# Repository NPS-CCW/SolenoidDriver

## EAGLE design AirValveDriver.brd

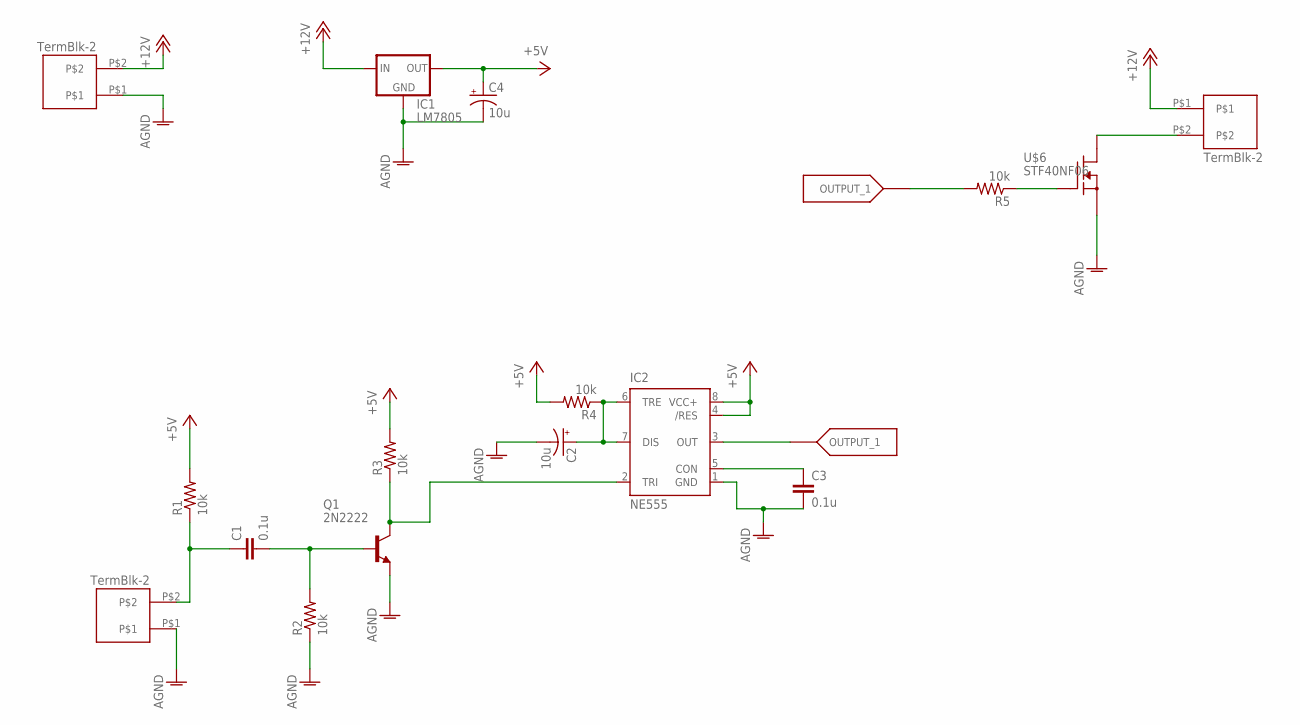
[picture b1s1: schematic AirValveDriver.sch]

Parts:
C1, C3: 0.1u; CCERAMIC_PKG
C2, C4: 10u; CPOL_PKG
IC1: LM7805; 78XXL
IC2: NE555; DIL-08
Q1: 2N2222; TO18
R1, R2, R3, R4, R5: 10k; RESISTOR_PKG
U$2, U$5: TB2; TB2_PKG
U$3: Pwr; TB2_PKG
U$6: STF40NF06; TO220H

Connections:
+5V: C4.+, IC1.OUT, IC2.4 (/RES), IC2.8 (VCC+), R1.2, R3.2, R4.2
+12V: IC1.IN, U$2.P$1, U$3.P$2
AGND: C2.-, C3.2, C4.-, IC1.GND, IC2.1 (GND), Q1.1 (E), R2.1, U$3.P$1, U$5.P$1, U$6.3 (S)
unnamed: C3.1, IC2.5 (CON)
unnamed: R5.1, U$6.1 (G)
unnamed: U$2.P$2, U$6.2 (D)
unnamed: C1.1, R1.1, U$5.P$2
unnamed: C1.2, Q1.2 (B), R2.2
unnamed: IC2.2 (TRI), Q1.3 (C), R3.1
unnamed: C2.+, IC2.6 (TRE), IC2.7 (DIS), R4.1
OUTPUT_1: IC2.3 (OUT), R5.2

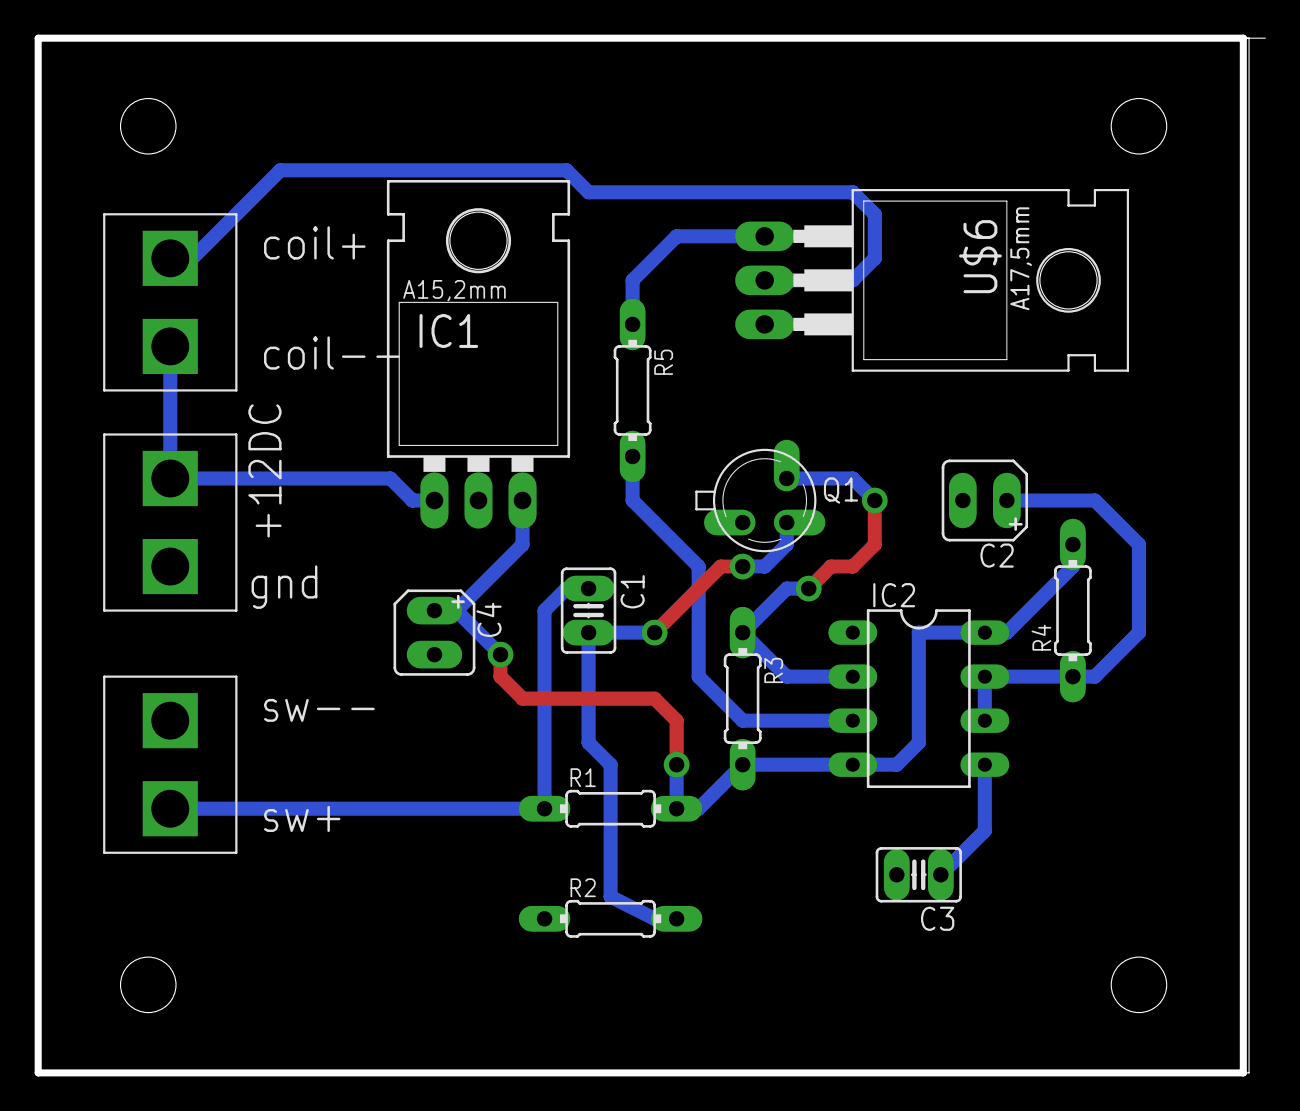
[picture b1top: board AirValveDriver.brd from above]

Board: 2 copper layers, 70.6 x 59.7 mm, 16 parts (0 on the bottom side), 11 nets.

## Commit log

2014-10-03 minor edits from the PCB mill computer
2014-10-05 added drill files after modifying the python script
    drill_mod is the drill file to load in the PCB Mill.
2014-10-06 added g_code for cutting bottom
2014-10-06 complete file set for v1
2014-10-09 updated after DRC
2014-10-09 mod board to use compliant drills
2014-10-15 updated cam files to run a copy of the board
2014-10-16 Final files we cut on Rev2
2014-11-10 Major changes as we work to produce this board
